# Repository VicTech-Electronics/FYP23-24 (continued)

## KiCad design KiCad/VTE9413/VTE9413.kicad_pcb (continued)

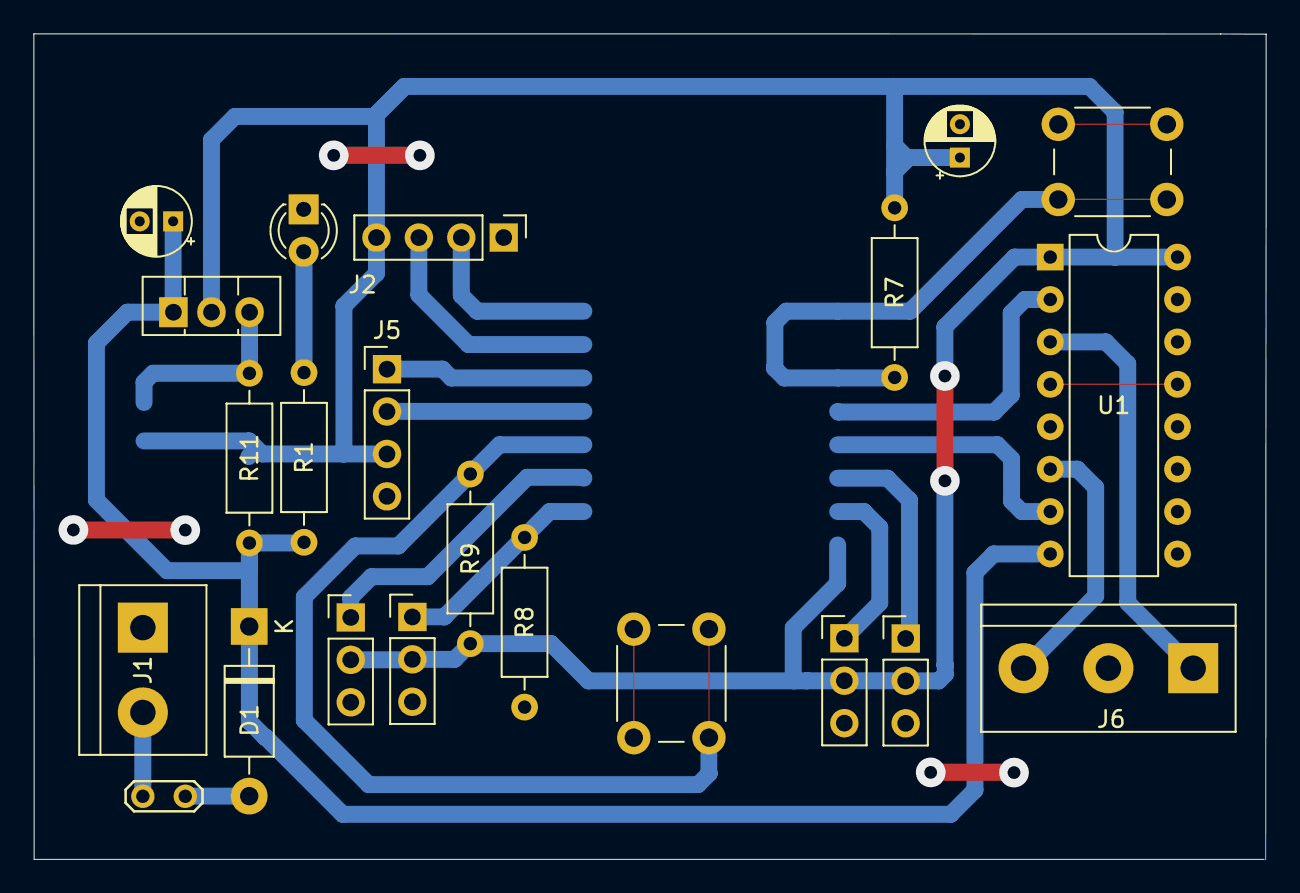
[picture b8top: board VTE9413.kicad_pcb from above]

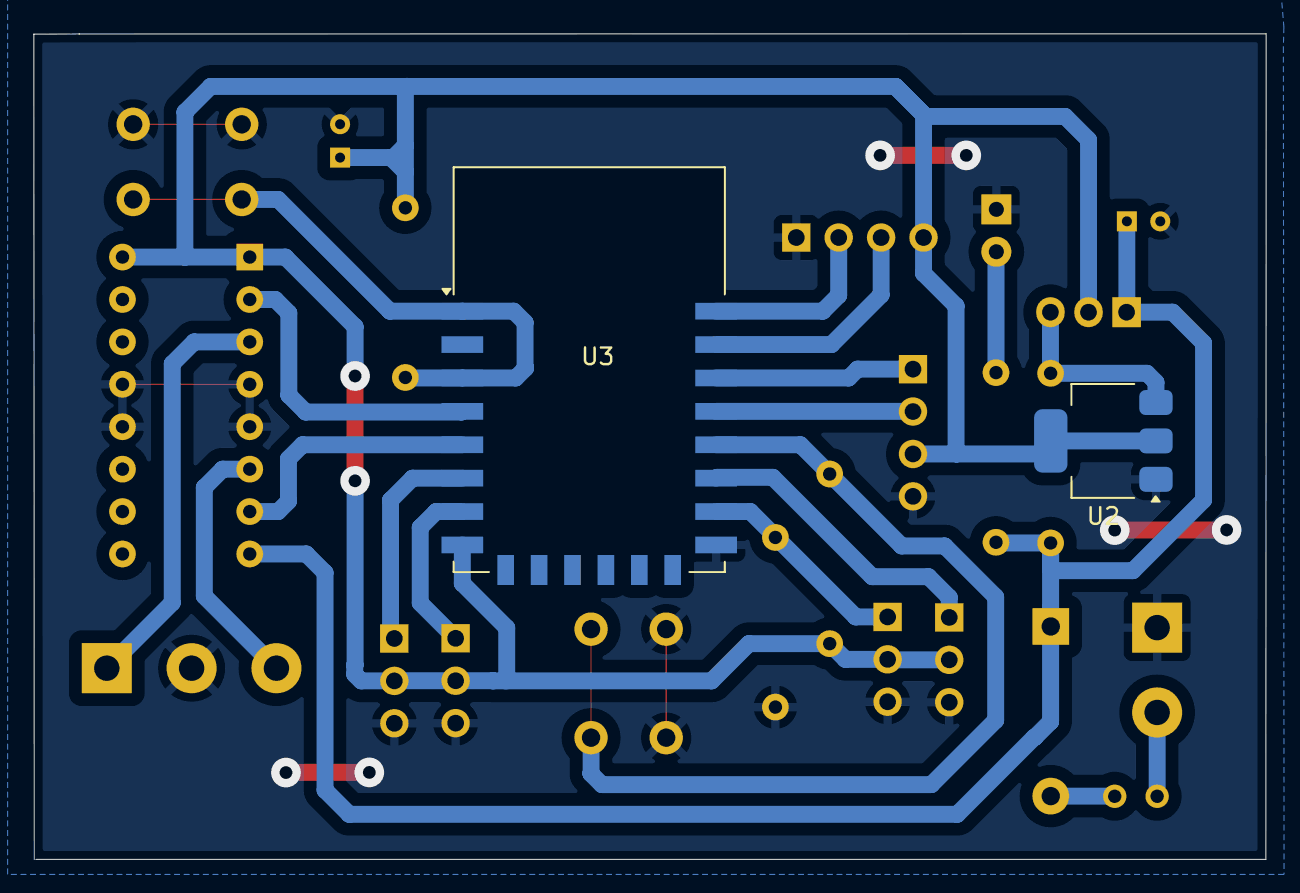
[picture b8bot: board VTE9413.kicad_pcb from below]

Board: 2 copper layers, 73.8 x 49.5 mm, 24 parts (2 on the bottom side), 21 nets.
